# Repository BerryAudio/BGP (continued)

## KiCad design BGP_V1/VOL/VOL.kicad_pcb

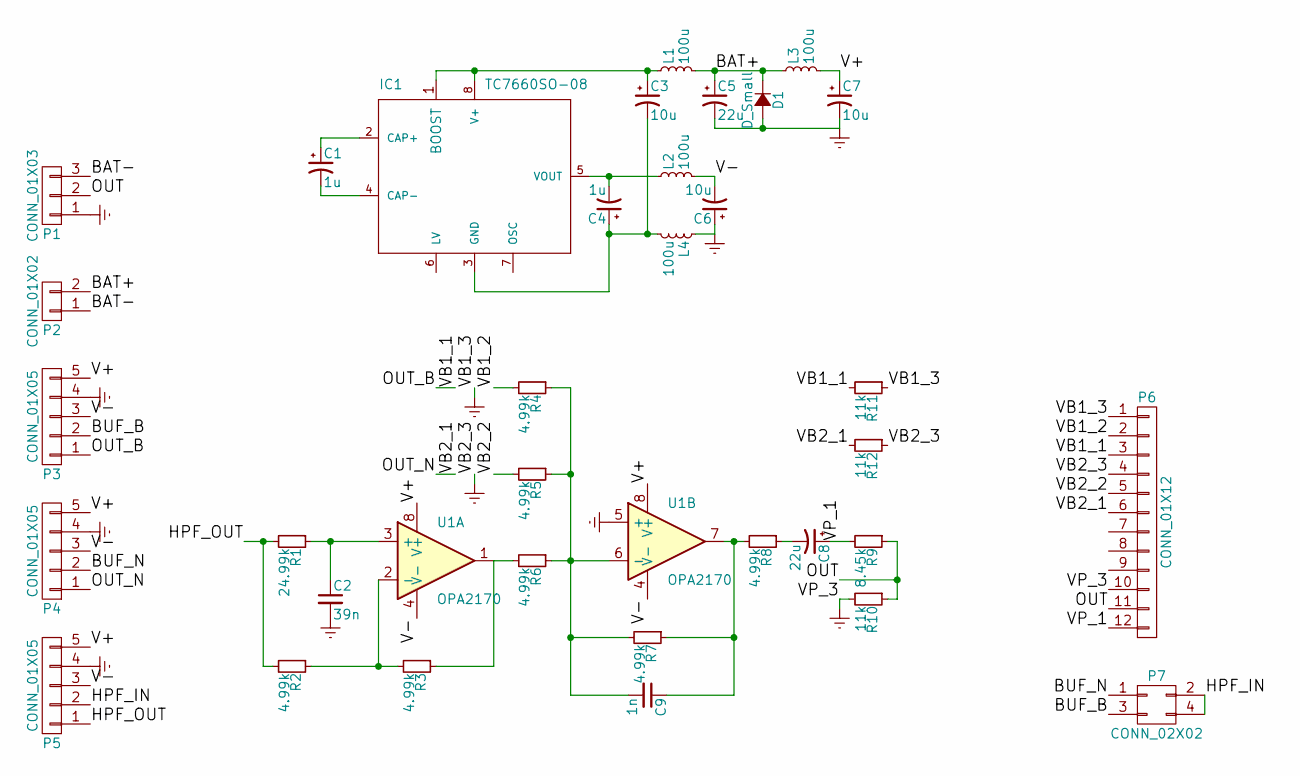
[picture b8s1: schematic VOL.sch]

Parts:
C1, C4: 1u; C_0805_HandSoldering
C2: 39n; C_1206_HandSoldering
C3, C6, C7: 10u; C_0805_HandSoldering
C5: 22u; C_0805_HandSoldering
C8: 22u; TantalC_SizeS_EIA-3216
C9: 1n; C_0603_HandSoldering
D1: D_Small; SOD-123
IC1: TC7660SO-08; SOIC-8_3.9x4.9mm_Pitch1.27mm
L1, L2, L3, L4: 100u; C_0805_HandSoldering
P1: CONN_01X03; TerminalBlock_Pheonix_MPT-2.54mm_3pol
P2: CONN_01X02; TerminalBlock_Pheonix_MPT-2.54mm_2pol
P3, P4, P5: CONN_01X05; Molex_MicroLatch-53253-0570_05x2.00mm_Straight
P6: CONN_01X12; Potentiometer_Alps_RK097_Quad_Vertical_Dual_Shaft
P7: CONN_02X02; Pin_Header_Straight_2x02_Pitch2.00mm
R1: 24.99k; R_0603_HandSoldering
R2, R3, R4, R5, R6, R7, R8: 4.99k; R_0603_HandSoldering
R9: 8.45k; R_0603_HandSoldering
R10, R11, R12: 11k; R_0603_HandSoldering
U1: OPA2170; SOIC-8_3.9x4.9mm_Pitch1.27mm

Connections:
/BAT+: C5.1, D1.1 (K), L1.2, L3.1, P2.2
/BAT-: P1.3, P2.1
/BUF_B: P3.2, P7.3
/BUF_N: P4.2, P7.1
/HPF_IN: P5.2, P7.2, P7.4
/HPF_OUT: P5.1, R1.2, R2.2
/OUT: P1.2, P6.11, R9.1, R10.1
/OUT_B: P3.1, P6.3, R11.2
/OUT_N: P4.1, P6.6, R12.2
/V+: C7.1, L3.2, P3.5, P4.5, P5.5, U1.8 (V+)
/V-: C6.2, L2.2, P3.3, P4.3, P5.3, U1.4 (V-)
/VB1_2: P6.2, R4.2
/VB2_2: P6.5, R5.2
/VP_1: C8.1, P6.12, R9.2
Earth: C2.2, C5.2, C6.1, C7.2, D1.2 (A), L4.1, P1.1, P3.4, P4.4, P5.4, P6.1, P6.4, P6.10, R10.2, R11.1, R12.1, U1.5 (+)
unnamed: C1.1, IC1.2 (CAP+)
unnamed: C1.2, IC1.4 (CAP-)
unnamed: C2.1, R1.1, U1.3 (+)
unnamed: C3.1, IC1.1 (BOOST), IC1.8 (V+), L1.1
unnamed: C3.2, C4.1, IC1.3 (GND), L4.2
unnamed: C4.2, IC1.5 (VOUT), L2.1
unnamed: C8.2, R8.1
unnamed: C9.1, R7.1, R8.2, U1.7
unnamed: C9.2, R4.1, R5.1, R6.1, R7.2, U1.6 (-)
unnamed: R2.1, R3.2, U1.2 (-)
unnamed: R3.1, R6.2, U1.1

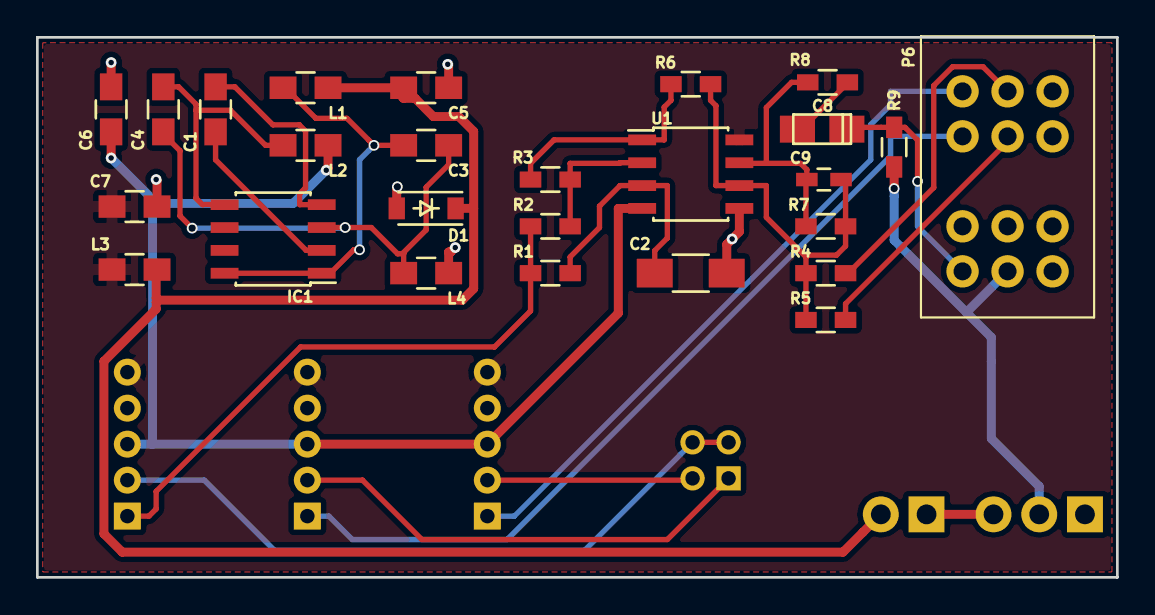
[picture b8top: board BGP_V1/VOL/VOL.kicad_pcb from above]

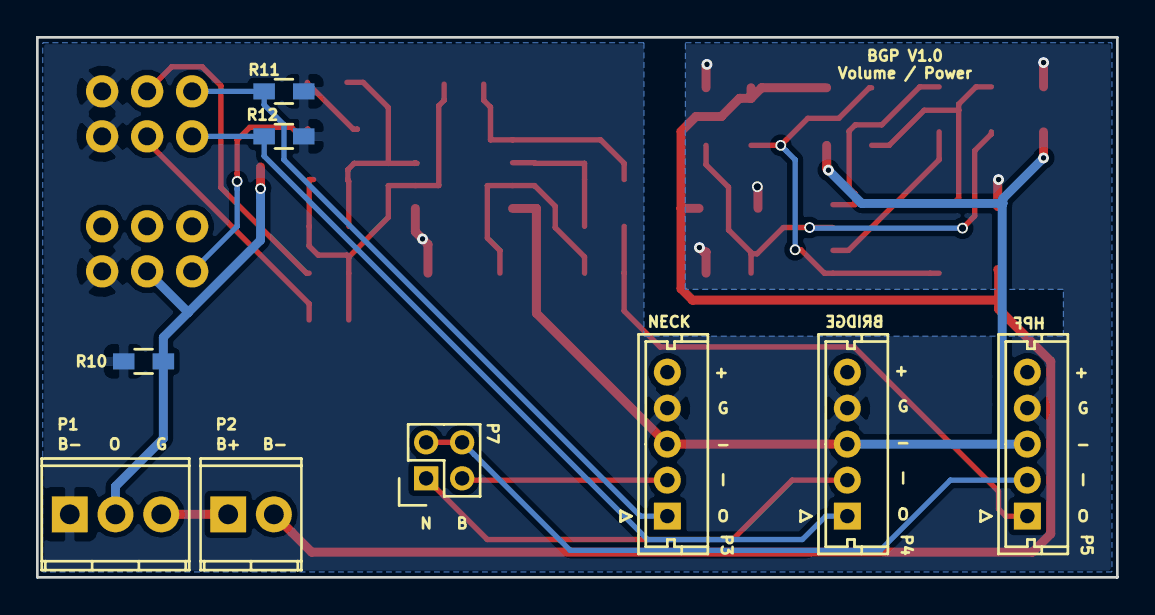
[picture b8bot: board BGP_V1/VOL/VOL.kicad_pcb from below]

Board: 2 copper layers, 60.0 x 30.0 mm, 35 parts (9 on the bottom side), 26 nets.
